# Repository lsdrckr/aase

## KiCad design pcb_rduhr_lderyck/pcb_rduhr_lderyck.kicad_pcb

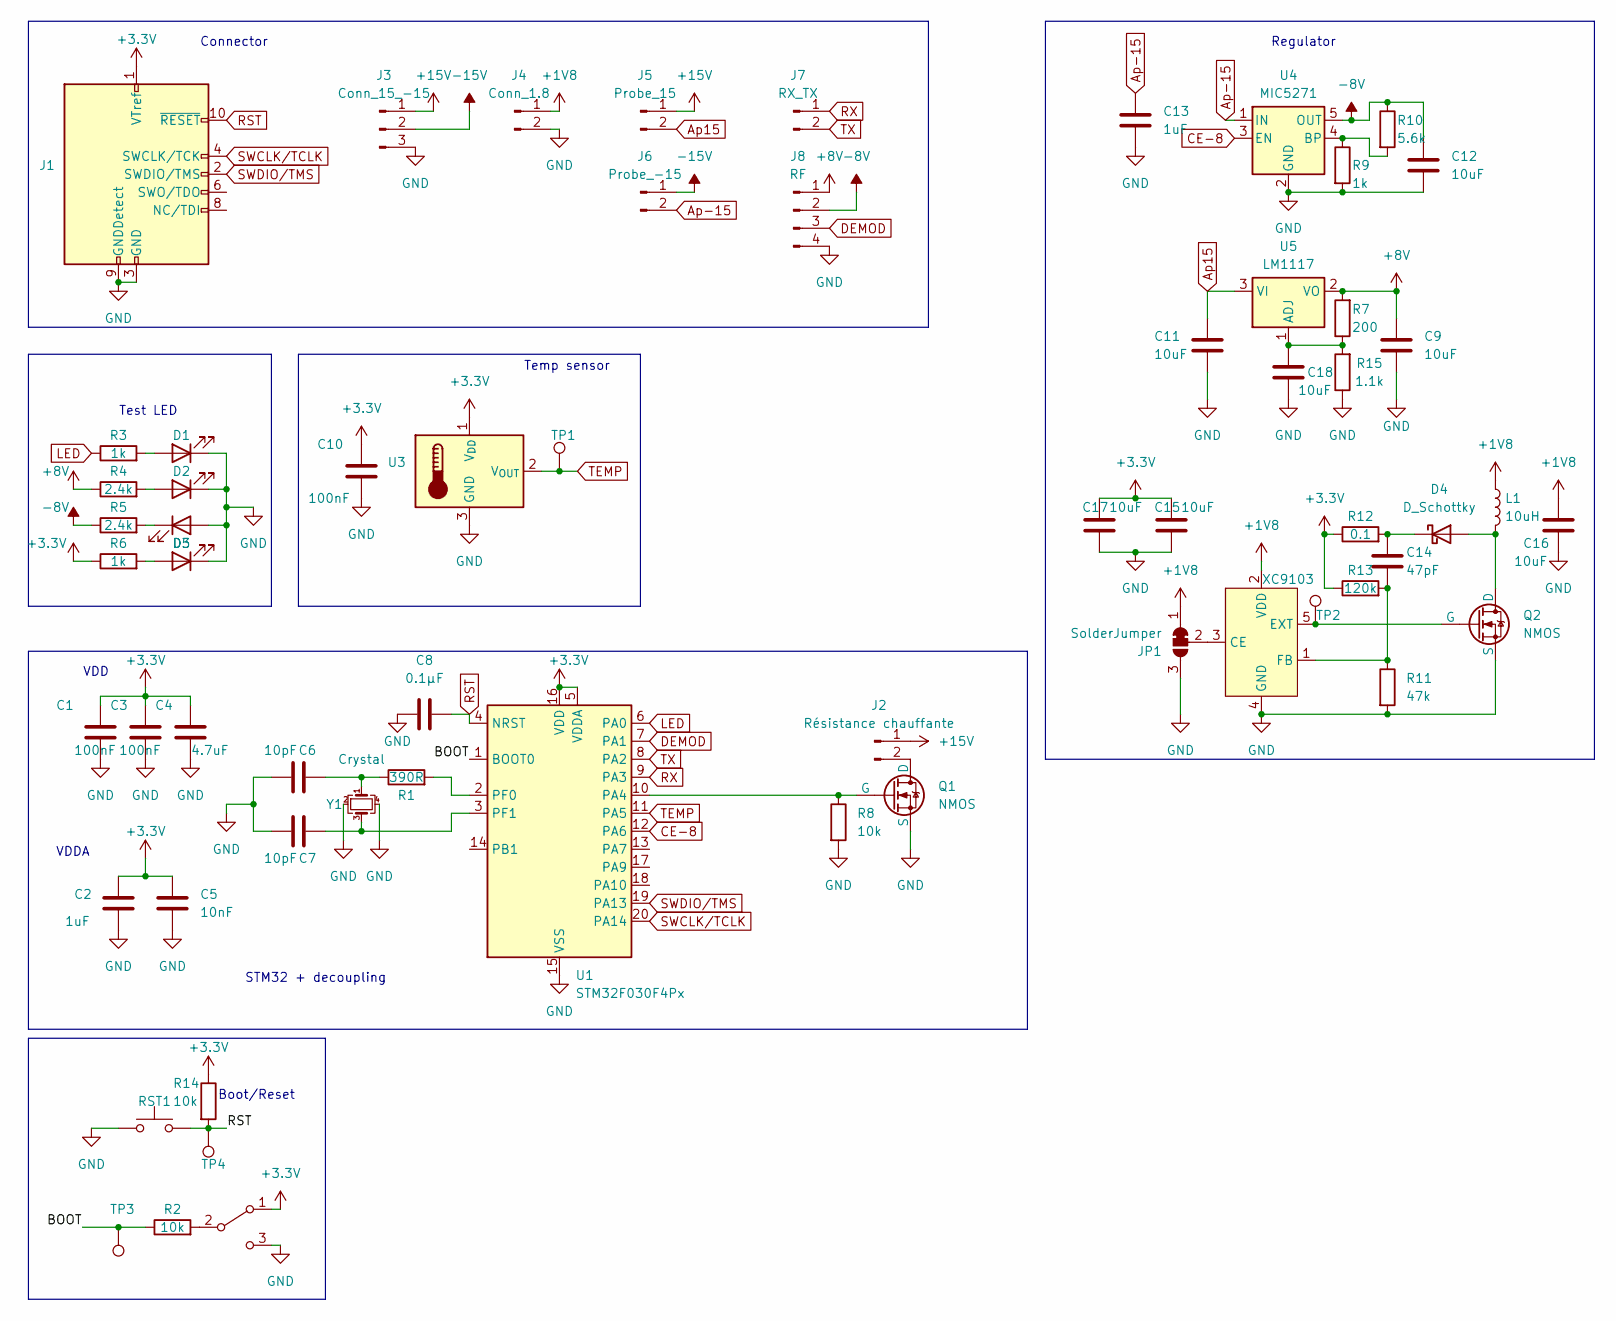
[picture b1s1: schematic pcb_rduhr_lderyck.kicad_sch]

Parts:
C1, C3, C10: 100nF; C_0603_1608Metric_Pad1.08x0.95mm_HandSolder
C2, C13: 1uF; C_0603_1608Metric_Pad1.08x0.95mm_HandSolder
C4: 4.7uF; C_0603_1608Metric_Pad1.08x0.95mm_HandSolder
C5: 10nF; C_0603_1608Metric_Pad1.08x0.95mm_HandSolder
C6, C7: 10pF; C_0603_1608Metric_Pad1.08x0.95mm_HandSolder
C8: 0.1µF; C_0603_1608Metric_Pad1.08x0.95mm_HandSolder
C9, C11, C12, C15, C16, C17, C18: 10uF; C_0603_1608Metric_Pad1.08x0.95mm_HandSolder
C14: 47pF; C_0603_1608Metric_Pad1.08x0.95mm_HandSolder
D1, D2, D3, D5: LED; D_0603_1608Metric_Pad1.05x0.95mm_HandSolder
D4: D_Schottky; DO-214AC
J1: Conn_ARM_JTAG_SWD_10; PinHeader_2x05_P2.54mm_Vertical
J2: Résistance chauffante; PinSocket_1x02_P2.54mm_Vertical
J3: Conn_15_-15; PinSocket_1x03_P2.54mm_Vertical
J4: Conn_1.8; PinSocket_1x02_P2.54mm_Vertical
J5: Probe_15; PinSocket_1x02_P2.54mm_Vertical
J6: Probe_-15; PinSocket_1x02_P2.54mm_Vertical
J7: RX_TX; PinSocket_1x02_P2.54mm_Vertical
J8: RF; PinSocket_1x04_P2.54mm_Vertical
JP1: SolderJumper; SolderJumper-3_P1.3mm_Bridged12_Pad1.0x1.5mm
L1: 10uH; 8.1_mm_x_7.3_mm_x_5.3_mm_Inductance
Q1, Q2: NMOS; SOT-89-3_Handsoldering
R1: 390R; R_0603_1608Metric_Pad0.98x0.95mm_HandSolder
R2, R8, R14: 10k; R_0603_1608Metric_Pad0.98x0.95mm_HandSolder
R3, R6, R9: 1k; R_0603_1608Metric_Pad0.98x0.95mm_HandSolder
R4, R5: 2.4k; R_0603_1608Metric_Pad0.98x0.95mm_HandSolder
R7: 200; R_0603_1608Metric_Pad0.98x0.95mm_HandSolder
R10: 5.6k; R_0603_1608Metric_Pad0.98x0.95mm_HandSolder
R11: 47k; R_0603_1608Metric_Pad0.98x0.95mm_HandSolder
R12: 0.1; R_0603_1608Metric_Pad0.98x0.95mm_HandSolder
R13: 120k; R_0603_1608Metric_Pad0.98x0.95mm_HandSolder
R15: 1.1k; R_0603_1608Metric_Pad0.98x0.95mm_HandSolder
RST1: SW_Push; SW_SPST_SKQG_WithStem
SW1: SW_DPDT_x2; PinHeader_1x03_P2.54mm_Vertical
TP1, TP2, TP3, TP4: TestPoint; TestPoint_Pad_D1.5mm
U1: STM32F030F4Px; TSSOP-20_4.4x6.5mm_P0.65mm
U3: MCP9700Ax-ETT; SOT-23
U4: MIC5271; SOT-23-5
U5: LM1117; SOT-223-3_TabPin2
XC9103: SOT25
Y1: Crystal; Crystal_SMD_3225-4Pin_3.2x2.5mm_HandSoldering

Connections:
+1V8: C16.1, J4.1, JP1.1 (A), L1.1, XC9103.2 (VDD)
+3.3V: C1.1, C2.1, C3.1, C4.1, C5.1, C10.1, C15.1, C17.1, J1.1 (VTref), R6.1, R12.1, R13.1, R14.1, SW1.1 (A), U1.5 (VDDA), U1.16 (VDD), U3.1 (V_{DD})
+8V: C9.1, J8.1, R4.1, R7.2, U5.2 (VO)
+15V: J2.1, J3.1, J5.1
-8V: C12.1, J8.2, R5.1, R10.1, U4.5 (OUT)
-15V: J3.2, J6.1
/BOOT: R2.1, TP3.1, U1.1 (BOOT0)
Ap15: C11.1, J5.2, U5.3 (VI)
Ap-15: C13.1, J6.2, U4.1 (IN)
CE-8: U1.12 (PA6), U4.3 (EN)
DEMOD: J8.3, U1.7 (PA1)
GND: C1.2, C2.2, C3.2, C4.2, C5.2, C6.2, C7.2, C8.1, C9.2, C10.2, C11.2, C12.2, C13.2, C15.2, C16.2, C17.2, C18.2, D1.1 (K), D2.1 (K), D3.2 (A), D5.1 (K), J1.3 (GND), J1.5 (GND), J1.9 (GNDDetect), J3.3, J4.2, J8.4, JP1.3 (B), Q1.3 (S), Q2.3 (S), R8.2, R9.2, R11.2, R15.1, RST1.1, SW1.3 (C), U1.15 (VSS), U3.3 (GND), U4.2 (GND), XC9103.4 (GND), Y1.2, Y1.4
LED: R3.1, U1.6 (PA0)
unnamed: C6.1, R1.1, Y1.1
unnamed: D1.2 (A), R3.2
unnamed: D2.2 (A), R4.2
unnamed: D3.1 (K), R5.2
unnamed: D4.2 (A), L1.2, Q2.1 (D)
unnamed: C14.1, D4.1 (K), R12.2
unnamed: D5.2 (A), R6.2
unnamed: J2.2, Q1.1 (D)
unnamed: JP1.2 (C), XC9103.3 (CE)
unnamed: Q1.2 (G), R8.1, U1.10 (PA4)
unnamed: Q2.2 (G), TP2.1, XC9103.5 (EXT)
unnamed: R2.2, SW1.2 (B)
unnamed: R1.2, U1.2 (PF0)
unnamed: C7.1, U1.3 (PF1), Y1.3
unnamed: R9.1, R10.2, U4.4 (BP)
unnamed: C18.1, R7.1, R15.2, U5.1 (ADJ)
unnamed: C14.2, R11.1, R13.2, XC9103.1 (FB)
RST: C8.2, J1.10 (~RESET), R14.2, RST1.2, TP4.1, U1.4 (NRST)
RX: J7.1, U1.9 (PA3)
SWCLK/TCLK: J1.4 (SWCLK/TCK), U1.20 (PA14)
SWDIO/TMS: J1.2 (SWDIO/TMS), U1.19 (PA13)
TEMP: TP1.1, U1.11 (PA5), U3.2 (V_{OUT})
TX: J7.2, U1.8 (PA2)

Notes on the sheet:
Connector
Regulator
STM32 + decoupling
Test LED
Temp sensor
VDD
VDDA
Boot/Reset

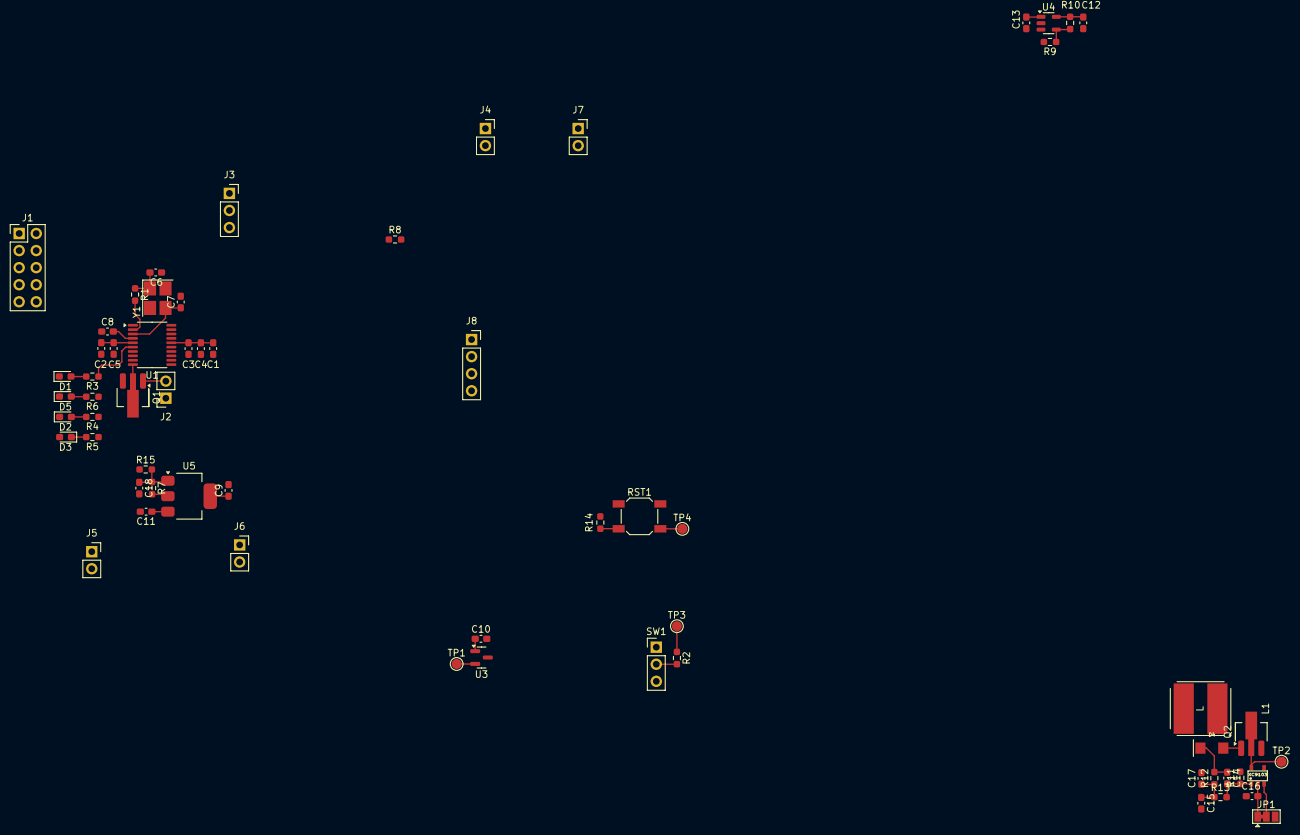
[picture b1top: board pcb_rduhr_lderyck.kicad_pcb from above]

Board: 2 copper layers, 62 parts (0 on the bottom side), 36 nets.

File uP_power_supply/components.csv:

"Reference","Value","Footprint","Datasheet","Sim.Device","Sim.Pins","Sim.Type","Qty"
"C1, C3, C10","100nF","Capacitor_SMD:C_0603_1608Metric_Pad1.08x0.95mm_HandSolder","~","","","","3"
"C2, C13","1uF","Capacitor_SMD:C_0603_1608Metric_Pad1.08x0.95mm_HandSolder","~","","","","2"
"C4","4.7uF","Capacitor_SMD:C_0603_1608Metric_Pad1.08x0.95mm_HandSolder","~","","","","1"
"C5","10nF","Capacitor_SMD:C_0603_1608Metric_Pad1.08x0.95mm_HandSolder","~","","","","1"
"C6, C7","10pF","Capacitor_SMD:C_0603_1608Metric_Pad1.08x0.95mm_HandSolder","~","","","","2"
"C8","0.1µF","Capacitor_SMD:C_0603_1608Metric_Pad1.08x0.95mm_HandSolder","~","","","","1"
"C9, C11, C12, C15-C18","10uF","Capacitor_SMD:C_0603_1608Metric_Pad1.08x0.95mm_HandSolder","~","","","","7"
"C14","47pF","Capacitor_SMD:C_0603_1608Metric_Pad1.08x0.95mm_HandSolder","~","","","","1"
"D1-D3, D5","LED","Diode_SMD:D_0603_1608Metric_Pad1.05x0.95mm_HandSolder","~","","","","4"
"D4","D_Schottky","footprints:DO-214AC","~","","","","1"
"J1","Conn_ARM_JTAG_SWD_10","Connector_PinHeader_2.54mm:PinHeader_2x05_P2.54mm_Vertical","http://infocenter.arm.com/help/topic/com.arm.doc.ddi0314h/DD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","","","","1"
"J2","Résistance chauffante","Connector_PinSocket_2.54mm:PinSocket_1x02_P2.54mm_Vertical","~","","","","1"
"J3","Conn_15_-15","Connector_PinSocket_2.54mm:PinSocket_1x03_P2.54mm_Vertical","~","","","","1"
"J4","Conn_1.8","Connector_PinSocket_2.54mm:PinSocket_1x02_P2.54mm_Vertical","~","","","","1"
"J5","Probe_15","Connector_PinSocket_2.54mm:PinSocket_1x02_P2.54mm_Vertical","~","","","","1"
"J6","Probe_-15","Connector_PinSocket_2.54mm:PinSocket_1x02_P2.54mm_Vertical","~","","","","1"
"J7","RX_TX","Connector_PinSocket_2.54mm:PinSocket_1x02_P2.54mm_Vertical","~","","","","1"
"J8","RF","Connector_PinSocket_2.54mm:PinSocket_1x04_P2.54mm_Vertical","~","","","","1"
"JP1","SolderJumper","Jumper:SolderJumper-3_P1.3mm_Bridged12_Pad1.0x1.5mm","~","","","","1"
"L1","10uH","footprints:8.1_mm_x_7.3_mm_x_5.3_mm_Inductance","~","","","","1"
"Q1, Q2","NMOS","Package_TO_SOT_SMD:SOT-89-3_Handsoldering","https://ngspice.sourceforge.io/docs/ngspice-html-manual/manu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","NMOS","1=D 2=G 3=S","VDMOS","2"
"R1","390R","Resistor_SMD:R_0603_1608Metric_Pad0.98x0.95mm_HandSolder","~","","","","1"
"R2, R8, R14","10k","Resistor_SMD:R_0603_1608Metric_Pad0.98x0.95mm_HandSolder","~","","","","3"
"R3, R6, R9","1k","Resistor_SMD:R_0603_1608Metric_Pad0.98x0.95mm_HandSolder","~","","","","3"
"R4, R5","2.4k","Resistor_SMD:R_0603_1608Metric_Pad0.98x0.95mm_HandSolder","~","","","","2"
"R7","200","Resistor_SMD:R_0603_1608Metric_Pad0.98x0.95mm_HandSolder","~","","","","1"
"R10","5.6k","Resistor_SMD:R_0603_1608Metric_Pad0.98x0.95mm_HandSolder","~","","","","1"
"R11","47k","Resistor_SMD:R_0603_1608Metric_Pad0.98x0.95mm_HandSolder","~","","","","1"
"R12","0.1","Resistor_SMD:R_0603_1608Metric_Pad0.98x0.95mm_HandSolder","~","","","","1"
"R13","120k","Resistor_SMD:R_0603_1608Metric_Pad0.98x0.95mm_HandSolder","~","","","","1"
"R15","1.1k","Resistor_SMD:R_0603_1608Metric_Pad0.98x0.95mm_HandSolder","~","","","","1"
"RST1","SW_Push","Button_Switch_SMD:SW_SPST_SKQG_WithStem","~","","","","1"
"SW1","SW_DPDT_x2","Connector_PinHeader_2.54mm:PinHeader_1x03_P2.54mm_Vertical","~","","","","1"
"TP1-TP4","TestPoint","TestPoint:TestPoint_Pad_D1.5mm","~","","","","4"
"U1","STM32F030F4Px","Package_SO:TSSOP-20_4.4x6.5mm_P0.65mm","https://www.st.com/resource/en/datasheet/stm32f030f4.pdf","","","","1"
"U3","MCP9700Ax-ETT","Package_TO_SOT_SMD:SOT-23","http://ww1.microchip.com/downloads/en/devicedoc/20001942g.pdf","","","","1"
"U4","MIC5271","Package_TO_SOT_SMD:SOT-23-5","http://ww1.microchip.com/downloads/en/DeviceDoc/20005785A.pdf","","","","1"
"U5","LM1117","Package_TO_SOT_SMD:SOT-223-3_TabPin2","http://www.ti.com/lit/ds/symlink/lm1117.pdf","","","","1"
"XC9103","~","footprints:SOT25","","","","","1"
"Y1","Crystal","Crystal:Crystal_SMD_3225-4Pin_3.2x2.5mm_HandSoldering","~","","","","1"

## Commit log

2024-04-05 PCB & datasheet & subject
2024-04-05 Carte uP quasi fini
2024-04-08 Update PCB 1
2024-04-10 Ajout simulation
2024-04-10 Update pcb alim 2
2024-04-10 RF Unit
2024-04-10 change(uP_power_supply) mv
2024-04-10 update rfunit phase shofter
2024-04-10 PCB microp prêt pour impression !
2024-04-10 Rangement gerber
2024-04-11 rm(simul_log)
2024-04-12 add(components)
